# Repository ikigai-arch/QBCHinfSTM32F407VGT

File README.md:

<div align="center">

# High-Gain Quadratic Boost Converter dengan H∞ Controller

**Desain perangkat keras (KiCad) dan firmware STM32F407VGT untuk QBC 18 V → 150 V
dengan pengendali mixed-sensitivity H∞ voltage-mode**

Repositori pendukung skripsi *Implementasi Hardware High-Gain Quadratic Boost Converter
dengan H∞ Controller* — Program Studi Teknik Elektro, Fakultas Teknik,
Universitas Negeri Semarang (2026).

</div>

---

## Daftar isi

- [Ringkasan](#ringkasan)
- [Spesifikasi sistem](#spesifikasi-sistem)
- [Struktur repositori](#struktur-repositori)
- [Perangkat keras (KiCad)](#perangkat-keras-kicad)
- [Firmware](#firmware)
- [Alur validasi MIL–SIL–PIL–hardware](#alur-validasi-milsilpilhardware)
- [Keselamatan](#keselamatan)
- [Sitasi](#sitasi)
- [Penulis](#penulis)

## Ringkasan

Quadratic Boost Converter (QBC) *single-switch* memberi penguatan
V<sub>o</sub>/V<sub>in</sub> = 1/(1 − D)², sehingga 18 V dapat dinaikkan ke 150 V
pada duty cycle sekitar 0,65 tanpa duty ekstrem. Fungsi alih duty-ke-keluaran QBC
memiliki zero di setengah bidang kanan dan resonansi teredam lemah, sehingga
repositori ini memakai **H∞ controller mixed-sensitivity voltage-mode** yang
hanya membutuhkan satu sensor tegangan keluaran.

Isi repositori:

1. **Desain board QBC lengkap di KiCad**: skematik hierarkis 5 lembar, layout PCB
   2 layer, pustaka simbol/footprint lokal, dan model 3D.
2. **Firmware kontroler** untuk STM32F407VGT (DevEBox) dalam dua versi, Arduino/STM32duino
   dan Keil/STM32 HAL. Kode kontrolernya (`controller_step.c`) sama persis dengan yang
   divalidasi pada MIL-2, SIL, dan PIL.
3. **Skrip MATLAB H∞** ([`matlab/`](matlab/)): sintesis mixed-sensitivity, diskretisasi,
   ekspor kode C, uji unit SIL, dan PIL lockstep.
4. **Pin map** yang mengikat firmware dan PCB ([`PINMAP.md`](PINMAP.md)).

## Spesifikasi sistem

| Parameter | Nilai |
|---|---|
| Tegangan masukan V<sub>in</sub> | 18 V |
| Tegangan keluaran V<sub>o</sub> | 150 V (D ≈ 0,654) |
| Beban nominal | R = 135 Ω (≈ 167 W) |
| Frekuensi switching f<sub>s</sub> | 10 kHz |
| Induktor L<sub>1</sub> / L<sub>2</sub> | 1 mH / 3 mH (operasi CCM) |
| Kapasitor C<sub>1</sub> / C<sub>2</sub> | 100 µF / 100 µF |
| Semikonduktor | MOSFET 650 V, dioda STTH8S06D (600 V, 8 A) |
| Gate driver | TLP250 (isolasi optik) + catu terisolasi B1215-3WR2 |
| Mikrokontroler | STM32F407VGT (DevEBox), PWM TIM1_CH1 @ PA8, ADC1_IN3 @ PA3 |
| Kontroler | H∞ diskret state-space orde 6, T<sub>s</sub> = 100 µs |
| Waktu eksekusi (PIL) | ≈ 3,6 µs per langkah (≈ 3,6 % periode kontrol) |
| Proteksi firmware | duty 0…0,65, OVP latch 165 V, input fault PD8, PWM mati saat boot |
| PCB | 2 layer, 150 × 175 mm, 125 footprint |

## Struktur repositori

```
.
├── hardware/
│   ├── kicad/                     proyek KiCad (buka Quadratic_Boost_Converter_v0.1.kicad_pro)
│   │   ├── *.kicad_sch            skematik hierarkis: root, high_voltage, analog,
│   │   │                          microcontroller, power_supply
│   │   ├── *.kicad_pcb            layout PCB 2 layer
│   │   └── lib/                   pustaka simbol & footprint lokal proyek
│   ├── schematic/                 ekspor PDF skematik (lengkap dan per lembar)
│   └── 3d/                        model 3D board (.glb) + penampil 3D di browser (index.html)
├── hil_stm32/                     firmware versi utama: Arduino IDE + STM32duino (USB CDC)
├── keil_hal/                      firmware versi cadangan: Keil uVision / STM32 HAL (USART3)
├── matlab/                        skrip H∞: sintesis → diskretisasi (MIL-2) → SIL (MEX) → PIL
├── docs/img/                      gambar untuk dokumentasi
└── PINMAP.md                      pin map DevEBox ↔ PCB QBC
```

## Perangkat keras (KiCad)

Proyek dibuat dengan **KiCad 10**. Buka
`hardware/kicad/Quadratic_Boost_Converter_v0.1.kicad_pro`. Semua footprint sudah
tertanam di file PCB, dan pustaka lokal yang dipakai disertakan di `hardware/kicad/lib/`
dengan path relatif (`${KIPRJMOD}`). Proyek bisa langsung dibuka di komputer lain
tanpa mengatur path pustaka.

| Lembar | Isi |
|---|---|
| Root | Hierarki utama, hubungan antarlembar, lubang mounting |
| `high_voltage` | Rangkaian daya QBC (L₁, L₂, C₁, C₂, D₁–D₃, MOSFET), relai masukan/keluaran, shunt arus |
| `analog` | Sensor tegangan masukan/keluaran, sensor arus masukan/keluaran, sensor suhu, filter anti-aliasing |
| `microcontroller` | Header DevEBox STM32F407VGT, alokasi pin PWM/ADC/GPIO |
| `power_supply` | Regulator board, catu op-amp, penggerak relai & kipas |

<details>
<summary><b>Pratinjau skematik</b> (klik untuk membuka)</summary>

**Hierarki utama**

**Rangkaian daya tegangan tinggi**

**Sensing analog**

**Mikrokontroler**

**Catu daya**

</details>

PDF skematik lengkap: [`hardware/schematic/QBC_schematic_full.pdf`](hardware/schematic/QBC_schematic_full.pdf).

**Model 3D.** [`hardware/3d/index.html`](hardware/3d/index.html) adalah penampil
3D mandiri (three.js) yang memuat model board. Unduh lalu buka di browser, atau buka
langsung lewat GitHub Pages jika sudah diaktifkan untuk repositori ini.
File `.glb` juga bisa dibuka di penampil glTF apa pun.

## Firmware

Ada dua versi firmware dengan pin, parameter, proteksi, dan perintah serial yang sama.
Pilih salah satu, karena flash yang satu akan menimpa yang lain.

| Versi | Toolchain | Serial | Status |
|---|---|---|---|
| [`hil_stm32/`](hil_stm32/) | Arduino IDE + STM32duino | USB CDC (micro-USB DevEBox) | **Utama, sudah diuji di board (PWM terverifikasi di osiloskop)** |
| [`keil_hal/`](keil_hal/) | Keil uVision / arm-none-eabi-gcc + STM32 HAL | USART3 (PB10/PB11) | Cadangan, terkompilasi, belum diuji di board |

Langkah kontrol setiap 100 µs:

```
ADC PA3 → Vo  ─┐
               ├─► controller_step(vref, vo) ─► duty (jepit 0…0,65) ─► TIM1 CCR (PA8, 10 kHz)
vref (ramp) ───┘
```

Perintah serial (115200 baud, diakhiri newline):

| Perintah | Fungsi |
|---|---|
| `e` | Mulai kontrol (vref naik dengan ramp dari Vo terukur) |
| `v<angka>` | Set vref target dalam volt, contoh `v50` (maks 150 V) |
| `d` | Stop dan reset / hapus FAULT |
| `p` | Tampilkan status |
| `k<angka>` | Kalibrasi pengali Vo, contoh `k0.98` |
| `m<angka>` / `a` | Uji meja: timpa Vo manual / kembali ke ADC |

Telemetri: `T,ms,state,vref,vo,duty,cycles,overrun` (state 0 = OFF, 1 = RUN, 2 = FAULT).
Petunjuk kompilasi dan flash ada di README masing-masing folder.

> `controller_step.c/.h` dan `controller_coeffs.h` dihasilkan dari sintesis H∞ di MATLAB
> ([`matlab/`](matlab/)) dan **tidak boleh diubah manual**. File yang sama dipakai di MIL-2, SIL, PIL, dan board.

## Alur validasi MIL–SIL–PIL–hardware

| Tahap | Konfigurasi | Kriteria / hasil |
|---|---|---|
| **MIL** | Model plant + kontroler kontinu/diskret di Simulink | Respons referensi, disturbance rejection, robustness |
| **SIL** | `controller_step()` dalam blok C Function Simulink (diuji unit lebih dulu via MEX terhadap `dlsim`) | max\|Δ\| ≈ 10⁻⁶ terhadap MATLAB; metrik dibandingkan dengan baseline MIL-2 |
| **PIL** | `controller_step.c` berjalan di STM32F407VGT, lockstep via USB CDC | Selisih duty terhadap MIL-2 < 10⁻⁷; eksekusi ≈ 3,6 µs |
| **Hardware** | Firmware di board QBC (repositori ini) | Bertahap: PWM → gate driver → power stage tegangan rendah → nominal |

Pengendali pembanding voltage-mode (PI respons frekuensi dan MPSO-PI) dirancang
dengan model plant, skenario uji, dan batas margin kestabilan yang sama.

## Keselamatan

Board ini menghasilkan **tegangan DC hingga 150 V**, yang berbahaya.

- Uji PWM dan gate driver lebih dulu tanpa power stage, lalu naikkan tegangan masukan bertahap.
- Pastikan duty 0 berarti MOSFET OFF dan OVP firmware aktif sebelum menyambung beban.
- Kapasitor keluaran dapat menyimpan muatan setelah sumber dimatikan; buang muatannya sebelum menyentuh board.

## Sitasi

```bibtex
@thesis{sinaga2026qbc,
  author  = {Yohanes Leonaldo Sinaga},
  title   = {Implementasi Hardware High-Gain Quadratic Boost Converter dengan H$\infty$ Controller},
  school  = {Universitas Negeri Semarang},
  type    = {Skripsi},
  year    = {2026},
  url     = {https://github.com/ikigai-arch/QBCHinfSTM32F407VGT}
}
```

## Penulis

- **Yohanes Leonaldo Sinaga** (NIM 2305100046): perancangan kontroler, firmware, validasi
- Pembimbing: **Rizky Ajie Aprilianto, S.Pd., M.Eng.**
- Tim capstone: Muhammad Arya Ardiansyah, Zieda Alfu Ni'am

Program Studi Teknik Elektro, Fakultas Teknik, Universitas Negeri Semarang.

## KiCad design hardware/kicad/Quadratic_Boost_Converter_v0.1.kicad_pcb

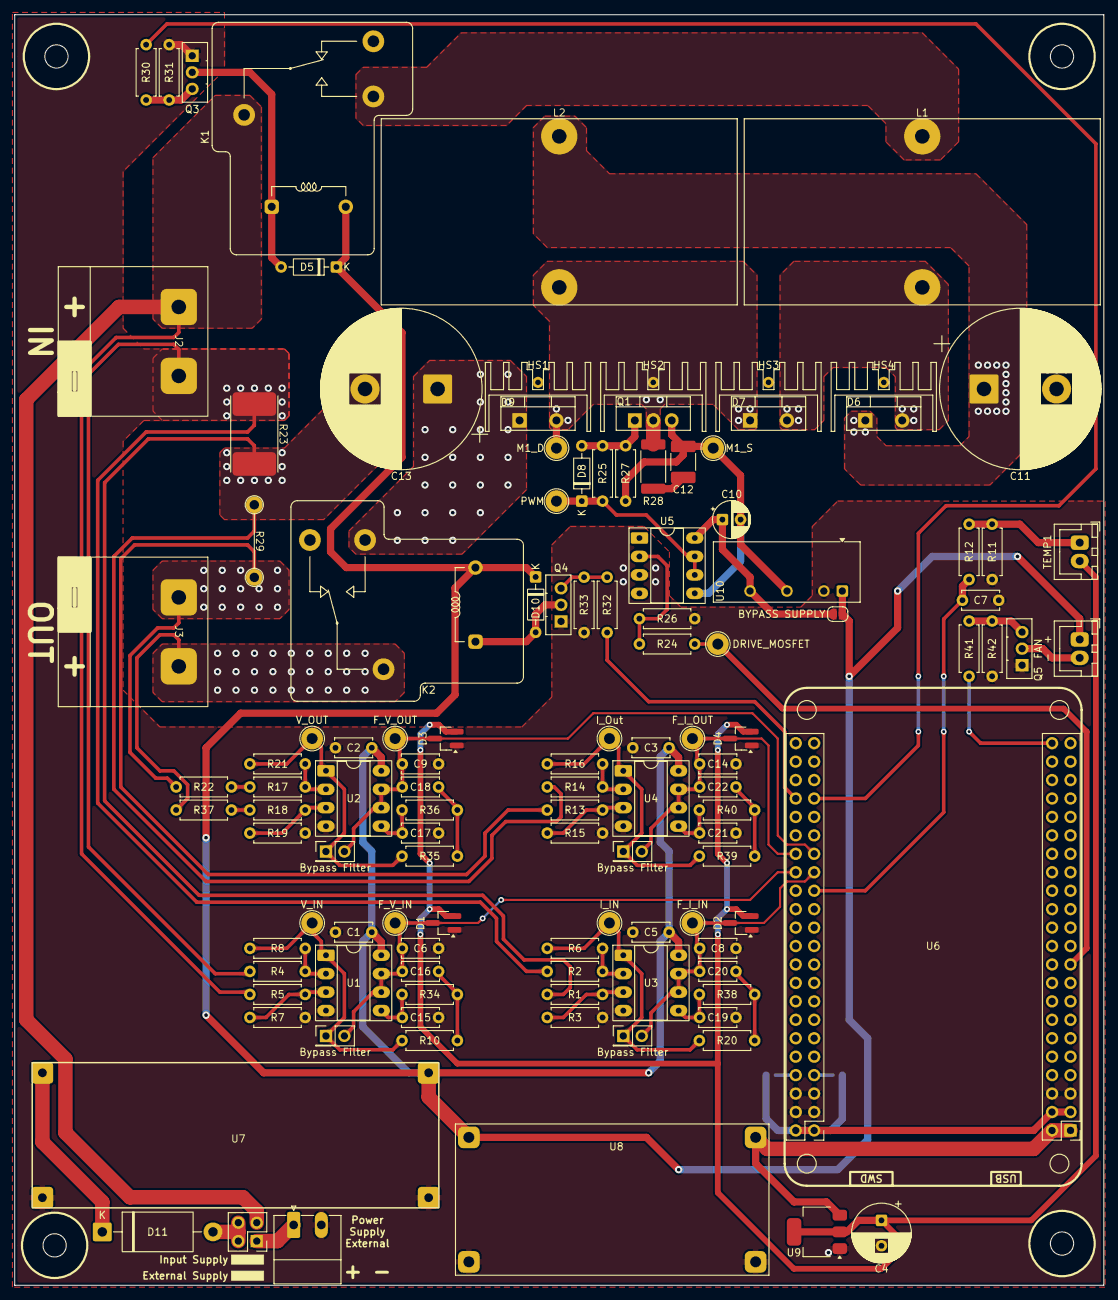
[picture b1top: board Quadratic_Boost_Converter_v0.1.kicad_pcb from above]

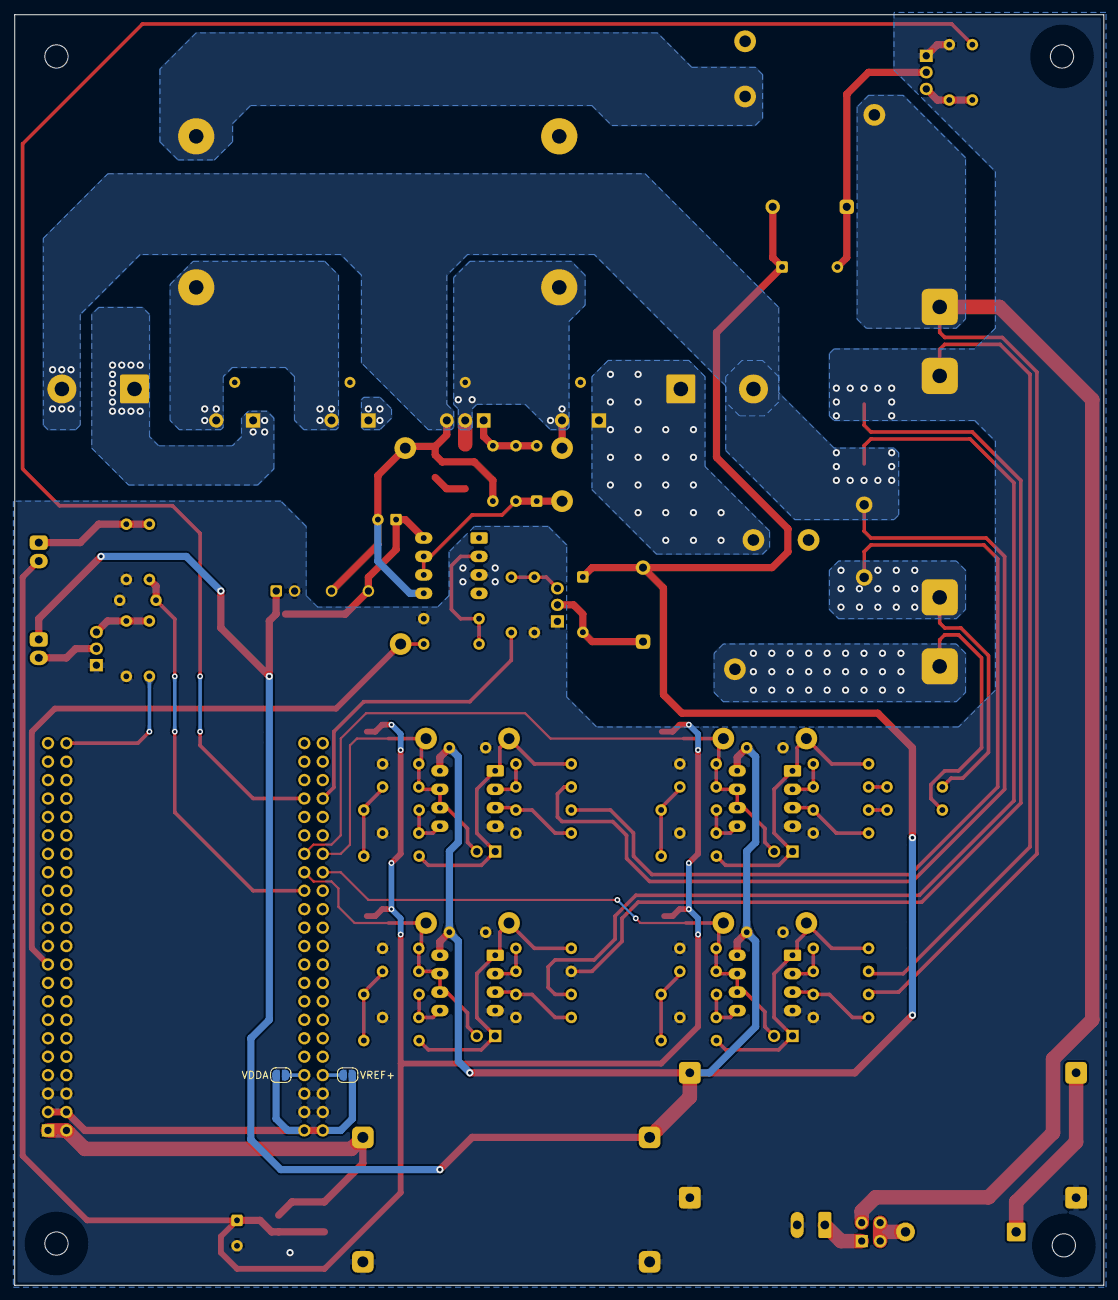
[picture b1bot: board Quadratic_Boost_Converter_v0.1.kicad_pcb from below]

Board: 2 copper layers, 150.0 x 175.0 mm, 125 parts (2 on the bottom side), 62 nets.

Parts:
C1, C2, C3, C5, C6, C7, C8, C9, C14: 100nF; C_Disc_D5.0mm_W2.5mm_P5.00mm
C4: 22uF; CP_Radial_D8.0mm_P3.50mm
C10: 1uF; CP_Radial_D5.0mm_P2.50mm
C11, C13: 100uF/450V; CP_Radial_D22.0mm_P10.00mm_SnapIn
C12: 2.2nF/250V; C_1812_4532Metric_Pad1.57x3.40mm_HandSolder
C15, C17, C19, C21: 6.8nF; C_Disc_D5.0mm_W2.5mm_P5.00mm
C16, C18, C20, C22: 3.9nF; C_Disc_D5.0mm_W2.5mm_P5.00mm
D1, D2, D3, D4: BAT54S; SOT-23_Handsoldering
D5, D8, D10: 1N4148; D_DO-35_SOD27_P7.62mm_Horizontal
D6, D7, D9: STTH8S06D; TO-220-2_Vertical
D11: US1M; D_DO-201_P15.24mm_Horizontal
H1, H2, H3, H4: MountingHole; MountingHole_3.2mm_M3
HS1, HS2, HS3, HS4: Heatsink; TO-220_HS
J1: TEMP1; JST_XH_B2B-XH-A_1X02_P2.54mm_DIY
J2: IN; HB9500_2P
J3: OUT; HB9500_2P
J4: FAN; JST_XH_B2B-XH-A_1X02_P2.54mm_DIY
J5: Supply Select; PinHeader_2x02_P2.54mm_Vertical
J6: External Supply; PhoenixContact_MC_1,5_2-G-3.81_1x02_P3.81mm_Horizontal
JP1, JP2, JP3, JP4: Bypass Filter; PinHeader_2x01_P2.54mm_Vertical
JP5: VDDA; SolderJumper-2_P1.3mm_Open_RoundedPad1.0x1.5mm
JP6: VREF+; SolderJumper-2_P1.3mm_Open_RoundedPad1.0x1.5mm
JP7: BYPASS SUPPLY; SolderJumper-2_P1.3mm_Open_RoundedPad1.0x1.5mm
K1, K2: RAYEX-L90S; Relay_SPDT_RAYEX-L90S
L1: 1mH; Inductor_Indo-MPPT
L2: 3mH; Inductor_Indo-MPPT
Q1: 45N65M5; TO-220-3_Vertical
Q3, Q4, Q5: D882; TO-126-3_Vertical
R1, R2, R13, R14: 1K 1%; R_Axial_DIN0207_L6.3mm_D2.5mm_P7.62mm_Horizontal
R3, R6, R15, R16: 30K 1%; R_Axial_DIN0207_L6.3mm_D2.5mm_P7.62mm_Horizontal
R4, R5: 100K 1%; R_Axial_DIN0207_L6.3mm_D2.5mm_P7.62mm_Horizontal
R7, R8, R10, R11, R19, R20, R21, R34, R35, R36, R38, R39, R40: 10K 1%; R_Axial_DIN0207_L6.3mm_D2.5mm_P7.62mm_Horizontal
R12: 3.9K 1%; R_Axial_DIN0207_L6.3mm_D2.5mm_P7.62mm_Horizontal
R17, R18, R22, R37: 300K 1%; R_Axial_DIN0207_L6.3mm_D2.5mm_P7.62mm_Horizontal
R23: 5mR; CSB392
R24: 470; R_Axial_DIN0207_L6.3mm_D2.5mm_P7.62mm_Horizontal
R25: 10R; R_Axial_DIN0207_L6.3mm_D2.5mm_P7.62mm_Horizontal
R26, R27: 10K; R_Axial_DIN0207_L6.3mm_D2.5mm_P7.62mm_Horizontal
R28: 10; R_2512_6332Metric_Pad1.40x3.35mm_HandSolder
R29: 20mR; Shunt_5
R30, R32, R41: 2K; R_Axial_DIN0207_L6.3mm_D2.5mm_P7.62mm_Horizontal
R31, R33, R42: 5.1K; R_Axial_DIN0207_L6.3mm_D2.5mm_P7.62mm_Horizontal
TP1: F_V_IN; TestPoint_Loop_D2.54mm_Drill1.5mm_Beaded
TP2: F_I_IN; TestPoint_Loop_D2.54mm_Drill1.5mm_Beaded
TP3: F_V_OUT; TestPoint_Loop_D2.54mm_Drill1.5mm_Beaded
TP4: F_I_OUT; TestPoint_Loop_D2.54mm_Drill1.5mm_Beaded
TP6: M1_D; TestPoint_Loop_D2.54mm_Drill1.5mm_Beaded
TP7: M1_S; TestPoint_Loop_D2.54mm_Drill1.5mm_Beaded
TP8: PWM; TestPoint_Loop_D2.54mm_Drill1.5mm_Beaded
TP9: V_OUT; TestPoint_Loop_D2.54mm_Drill1.5mm_Beaded
TP10: V_IN; TestPoint_Loop_D2.54mm_Drill1.5mm_Beaded
TP11: I_IN; TestPoint_Loop_D2.54mm_Drill1.5mm_Beaded
TP12: I_Out; TestPoint_Loop_D2.54mm_Drill1.5mm_Beaded
TP13: DRIVE_MOSFET; TestPoint_Loop_D2.54mm_Drill1.5mm_Beaded
U1, U2, U3, U4: LM2904; DIP-8_W7.62mm_Socket_LongPads
U5: TLP250; DIP-8_W7.62mm_Socket_LongPads
U6: STM32F407VGT_DevEBox; DevEBox_STM32F407VGT
U7: Buck-Boost_Module; Buck_Boost_Module
U8: LM2596; LM2596 (1)
U9: AMS1117-3.3; SOT-223-3_TabPin2
U10: B1215-3WR2; Converter_DCDC_TRACO_TRA3-xxxx_THT

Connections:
+3.3V: C4.1, D1.2 (K), D2.2 (K), D3.2 (K), D4.2 (K), J1.2, U9.2 (VO)
+3V3: JP5.2 (B), JP6.2 (B), U6.3 (+3V3), U6.4 (+3V3), U6.45 (+3V3), U6.46 (+3V3)
+5V: U6.1 (+5V), U6.2 (+5V), U8.3 (OUT+), U9.3 (VI)
+12V: C1.1, C2.1, C3.1, C5.1, D5.1 (K), D10.1 (K), J4.1, JP7.1 (A), K1.A2, K2.A2, U1.8 (V+), U2.8 (V+), U3.8 (V+), U4.8 (V+), U7.3 (OUT+), U8.1 (IN+), U10.1 (+Vin)
+15V: C10.1, JP7.2 (B), U5.8 (VCC), U10.6 (+Vout)
/Analog/I_IN: C8.1, C20.2, D2.3 (COM), JP1.2 (B), TP2.1 (1_1), U3.6 (-), U3.7, U6.73 (PA5)
/Analog/I_OUT: C14.1, C22.2, D4.3 (COM), JP2.2 (B), TP4.1 (1_1), U4.6 (-), U4.7, U6.76 (PA2)
/Analog/OUTPUT+: J3.2, K2.11, R37.1
/Analog/OUTPUT-: J3.1, R13.1, R22.1, R29.2
/Analog/TEMP1: C7.1, R12.2, U6.71 (PA7)
/Analog/V_IN: C6.1, C16.2, D1.3 (COM), JP3.2 (B), TP1.1 (1_1), U1.6 (-), U1.7, U6.74 (PA4)
/Analog/V_OUT: C9.1, C18.2, D3.3 (COM), JP4.2 (B), TP3.1 (1_1), U2.6 (-), U2.7, U6.75 (PA3)
/High Voltage/DRIVE_MOSFET: R24.1, TP13.1 (1_1), U6.19 (PA8)
/High Voltage/D_MOS: D7.1 (K), D9.2 (A), HS2.1, L2.2, Q1.2 (D), R28.2, TP6.1 (1_1)
/High Voltage/Fan: R41.1, U6.44 (PE0)
/High Voltage/GND_MOS: C10.2, C11.2, C12.2, C13.2, Q1.3 (S), R1.1, R14.1, R23.2, R27.1, R29.1, TP7.1 (1_1), U5.5 (VEE), U10.4 (-Vout)
/High Voltage/K_Input: D5.2 (A), K1.A1, Q3.2 (C)
/High Voltage/K_Output: D10.2 (A), K2.A1, Q4.2 (C)
/High Voltage/PWM: D8.1 (K), R25.1, TP8.1 (1_1), U5.6 (VO), U5.7 (VO)
/High Voltage/Relay_Input: R30.1, U6.81 (PC1)
/High Voltage/Relay_Output: R32.1, U6.82 (PC0)
GND: C1.2, C2.2, C3.2, C4.2, C5.2, C6.2, C7.2, C8.2, C9.2, C14.2, C15.2, C17.2, C19.2, C21.2, D1.1 (A), D2.1 (A), D3.1 (A), D4.1 (A), J2.2, J6.2, Q3.1 (E), Q4.1 (E), Q5.1 (E), R2.1, R3.2, R4.1, R7.2, R11.1, R15.2, R19.2, R23.1, R26.1, R31.2, R33.2, R42.2, U1.4 (V-), U2.4 (V-), U3.4 (V-), U4.4 (V-), U5.3 (C), U6.5 (VSS), U6.6 (VSS), U6.47 (VSS), U6.48 (VSS), U6.49 (VSS), U6.50 (VSS), U7.2 (IN-), U7.4 (OUT-), U8.2 (IN-), U8.4 (OUT-), U9.1 (GND), U10.2 (-Vin)
unnamed: C12.1, R28.1
unnamed: C16.1, R10.2, R34.1
unnamed: C18.1, R35.2, R36.1
unnamed: C20.1, R20.2, R38.1
unnamed: C22.1, R39.2, R40.1
unnamed: D6.2 (A), D7.2 (A), L1.2
unnamed: C11.1, D6.1 (K), L2.1
unnamed: D8.2 (A), Q1.1 (G), R25.2, R27.2
unnamed: C13.1, D9.1 (K), K2.14
unnamed: D11.2 (A), J5.2, J5.4
unnamed: D11.1 (K), U7.1 (IN+)
unnamed: J1.1, R11.2, R12.1
unnamed: J4.2, Q5.2 (C)
unnamed: J5.1, J6.1
unnamed: JP1.1 (A), R6.2, R20.1, TP11.1 (1_1), U3.1
unnamed: JP2.1 (A), R16.2, R39.1, TP12.1 (1_1), U4.1
unnamed: JP3.1 (A), R8.2, R10.1, TP10.1 (1_1), U1.1
unnamed: JP4.1 (A), R21.2, R35.1, TP9.1 (1_1), U2.1
unnamed: JP5.1 (A), U6.51 (VDDA)
unnamed: JP6.1 (A), U6.52 (VREF)
unnamed: K1.14, L1.1
unnamed: Q3.3 (B), R30.2, R31.1
unnamed: Q4.3 (B), R32.2, R33.1
unnamed: Q5.3 (B), R41.2, R42.1
unnamed: R17.1, R22.2
unnamed: R18.1, R37.2
unnamed: R5.2, R7.1, U1.3 (+)
unnamed: R4.2, R8.1, U1.2 (-)
unnamed: C15.1, R34.2, U1.5 (+)
unnamed: R18.2, R19.1, U2.3 (+)
unnamed: R17.2, R21.1, U2.2 (-)
unnamed: C17.1, R36.2, U2.5 (+)
unnamed: R1.2, R3.1, U3.3 (+)
unnamed: R2.2, R6.1, U3.2 (-)
unnamed: C19.1, R38.2, U3.5 (+)
unnamed: R13.2, R15.1, U4.3 (+)
unnamed: R14.2, R16.1, U4.2 (-)
unnamed: C21.1, R40.2, U4.5 (+)
unnamed: R24.2, R26.2, U5.2 (A)
VDC: J2.1, J5.3, K1.11, R5.1

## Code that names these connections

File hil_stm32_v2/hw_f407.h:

/* hw_f407.h -- lapisan perangkat keras STM32F407VGT untuk board QBC v2 (register-level).
 * Pin (dicek terhadap netlist KiCad v0.1, pad U6; lihat REVIEW_firmware_v1.md):
 *   PA8  TIM1_CH1  DRIVE_MOSFET -> R24 470 -> LED TLP250 (R26 10k pull-down) : aktif HIGH
 *   PA3  ADC1_IN3  V_OUT  (setelah relai K2!)
 *   PA5  ADC1_IN5  I_IN   (shunt R23 5 mOhm, jalur balik)
 *   PA4  ADC1_IN4  V_IN   (sebelum relai K1)
 *   PA2  ADC1_IN2  I_OUT  (shunt R29 20 mOhm)
 *   PA7  ADC1_IN7  TEMP1  (NTC)
 *   PC1  K1 Relay_Input  (aktif HIGH, D882, pull-down basis 5,1k -> OFF saat reset)
 *   PC0  K2 Relay_Output (idem)
 *   PE0  Kipas            (idem)
 *   PE6  TRIG (bebas di PCB)  pulsa 1 ms saat step Vref / perintah trig
 *   PE9  ISR  (bebas di PCB)  HIGH selama ISR kontrol (lihat saat cuplik & waktu eksekusi)
 */
#ifndef HW_F407_H
#define HW_F407_H
#include <stdint.h>
#ifdef __cplusplus
extern "C" {
#endif

void     hw_safe_gpio_early(void);   /* PANGGIL PALING AWAL: semua keluaran daya LOW */
void     hw_init(void);              /* TIM1 PWM 10 kHz + ADC1 injected + NVIC; PWM tetap mati */
void     hw_iwdg_start(void);        /* watchdog ~100 ms (tidak bisa dimatikan setelah start) */
void     hw_service(uint32_t now_ms);/* dari loop: watchdog + deteksi ISR macet + statistik */
void     hw_kill(void);              /* PWM mati (MOE=0) + K1 dibuka, langsung di register */
uint32_t hw_isr_count(void);
uint32_t hw_overruns(void);
uint32_t hw_isr_cycles(void);
uint32_t hw_sysclk(void);
int      hw_clock_is_hse(void);
const char *hw_reset_cause(void);    /* dibaca sekali saat boot */
uint32_t qbc_hw_cycles(void);        /* DWT->CYCCNT */

#ifdef __cplusplus
}
#endif
#endif
